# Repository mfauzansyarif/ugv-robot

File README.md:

# UGV Lidikzi 2

Sistem kendali *Unmanned Ground Vehicle* (UGV) remote-control untuk TNI Zeni AD. Robot dikendalikan operator lewat GCS (Ground Control Station) touchscreen yang terhubung ke robot lewat radio RF, dengan STM32 sebagai "hub" hardware dan Jetson Nano (ROS2) sebagai "otak" pengambil keputusan.

Dokumentasi ini mencakup arsitektur, protokol komunikasi, cara build/flash/jalanin tiap komponen, dan tools testing yang tersedia.

---

## Daftar Isi

1. [Ringkasan Fitur](#ringkasan-fitur)
2. [Arsitektur Sistem](#arsitektur-sistem)
3. [Struktur Repository](#struktur-repository)
4. [Komponen Hardware](#komponen-hardware)
5. [Protokol Komunikasi](#protokol-komunikasi)
6. [Firmware STM32](#firmware-stm32)
7. [ROS2 (Jetson Nano)](#ros2-jetson-nano)
8. [GCS App (Ground Control Station)](#gcs-app-ground-control-station)
9. [Cara Build & Flash STM32](#cara-build--flash-stm32)
10. [Cara Jalankan ROS2](#cara-jalankan-ros2)
11. [Cara Jalankan GCS App](#cara-jalankan-gcs-app)
12. [Tools Testing](#tools-testing)
13. [Isu & Catatan Penting](#isu--catatan-penting)

---

## Ringkasan Fitur

- Kendali gerak (drive + steering) lewat joystick analog di panel GCS
- 8 actuator linear individual (steering depan/belakang kiri-kanan, body depan/belakang kiri-kanan) - bisa dikalibrasi satu-satu, atau digerakkan berpasangan per-axle buat kenyamanan
- Pan-tilt kamera + zoom (Sony FCB-EV7520 lewat modul joystick/RS485)
- Laser Range Finder (Noptel LRF127) - baca jarak on-demand + pointer ON/OFF - ⚠️ **masih develop, lihat [Isu & Catatan Penting](#isu--catatan-penting)**
- Lampu depan (dimmable) + lampu belakang (mati/nyala/kedip, otomatis kedip pas mundur)
- Slip ring power switch (buat pantilt+kamera+LRF yang duduk di dudukan berputar) - ⚠️ **butuh jeda tunggu setelah dinyalain, lihat [Isu & Catatan Penting](#isu--catatan-penting)**
- Mode kalibrasi actuator (Fully Extend + Fully Left) - ⚠️ **durasi timeout-nya belum di-set, lihat [Isu & Catatan Penting](#isu--catatan-penting)**
- Deteksi orang otomatis (YOLO/TensorRT) buat overlay video, mode manual/auto - ⚠️ **masih develop, belum diimplementasi (butuh spek Jetson lebih tinggi)**
- E-STOP manual + beberapa lapis failsafe otomatis (link timeout, auto-estop kalau telemetry putus, dll - lihat [Isu & Catatan Penting](#isu--catatan-penting))

---

## Arsitektur Sistem

Prinsip desain: **"dumb driver, smart brain"** - STM32 gak pernah mutusin apa-apa sendiri (kecuali failsafe darurat), semua logic ada di `core_node.py` (Jetson). STM32 cuma nge-apply command final dan me-relay data mentah.

```mermaid
flowchart LR
    subgraph GCS["GCS Touchscreen (Asus NUC / laptop)"]
        Arduino["Arduino Mega Pro<br/>(panel fisik: joystick,<br/>tombol, switch)"]
        App["GCS App (PySide6)<br/>main.py / main_window.py"]
        Arduino -- "Serial USB<br/>(frame mentah panel)" --> App
    end

    App == "RF Radio<br/>USART2 @ 57600<br/>15B request / 11B reply<br/>+ checksum" ==> STM

    subgraph STM["STM32 G474RE (HUB)"]
        direction TB
        M["main.c<br/>dumb driver + failsafe"]
    end

    STM == "UART langsung<br/>USART3 @ 115200<br/>27B down / 20B up<br/>+ checksum XOR" ==> Jetson

    subgraph Jetson["Jetson Nano (OTAK - ROS2)"]
        direction TB
        SIN["stm32_interface_node<br/>(translator byte<->topic)"]
        CN["core_node<br/>(SATU-SATUNYA logic)"]
        SIN <-. topics .-> CN
    end

    STM == "RS485 bus<br/>USART1 @ 9600<br/>Pelco-D style, 7B/frame" ==> RS485

    subgraph RS485["Bus RS485 Bersama"]
        Pantilt["Pantilt<br/>(protokol custom)"]
        Kamera["Kamera<br/>Sony FCB-EV7520<br/>(Pelco-D->VISCA)"]
        Bridge["Bridge LRF<br/>NUCLEO-G431KB<br/>(addr=2)"]
    end

    Bridge -- "UART langsung<br/>native protocol" --> LRF["LRF127 (Noptel)<br/>laser rangefinder"]

    STM -- "Motor driver" --> Motors["4x Motor AC (PULS+SIGN)<br/>Houle Servo Driver"]
    STM -- "H-bridge digital" --> Act["8x Linear Actuator<br/>TiMOTION JP4"]
    STM -- PWM --> Lamps["Lampu depan/belakang"]
```

**Kenapa arsitektur ini:** desain awal sempat coba SPI dan I2C langsung ke Jetson, gagal secara elektrik. Mentor minta USB Jetson jangan dipakai buat link real-time (cuma boleh buat flashing sesekali) - jadi semua link fisik (RF, RS485) dipegang STM32, Jetson cuma dapat 1 link UART biasa ke STM32.

Node `cv_node` (deteksi orang YOLO/TensorRT) direncanakan tapi **belum diimplementasi** - lihat [Isu & Catatan Penting](#isu--catatan-penting).

Diagram block versi visual (drawio) juga ada di [`Dokumentasi/Block Diagram.png`](Dokumentasi/Block%20Diagram.png).

---

## Struktur Repository

Repo sudah dirapikan jadi struktur flat tunggal - semua yang ada di root INI yang aktif dipakai, gak ada lagi folder arsip/duplikat legacy.

```
ugv-robot/
├── Code/
│   ├── NucleoG474RE/           # Firmware STM32 G474RE (MASTER/HUB) - STM32CubeIDE project
│   ├── NucleoG431KB/           # Firmware STM32 G431KB (BRIDGE LRF) - STM32CubeIDE project
│   ├── ArduinoMegaPro/         # Firmware panel GCS fisik (joystick+tombol -> serial)
│   ├── Asus NUC/               # GCS App (PySide6, Python) - jalan di laptop/NUC
│   └── Jetson Nano/            # (kosong - node ROS2 ada di ROS2/ros2_ws, bukan di sini)
├── Datasheet/                  # Datasheet semua komponen (LRF127, servo driver, actuator, dst)
├── Dokumentasi/                # Block diagram + dokumentasi lama
├── Hardware/                   # Layout panel GCS, gambar rangka
├── ROS2/
│   ├── PANDUAN_JALANKAN_ROS2.txt
│   └── ros2_ws/                # Workspace ROS2 (src/ + build/install/log kalau sudah di-colcon build)
├── Schematic/                  # Skematik KiCad/EasyEDA board custom STM32G474
└── Test Code/                  # Kumpulan skrip tes Python/Arduino (satu lokasi, histori lengkap)
```

---

## Komponen Hardware

| Komponen | Model | Peran |
|---|---|---|
| MCU Hub | STM32G474RE (custom board berbasis Nucleo) | Master - kendaliin motor, actuator, lampu, relay semua link |
| MCU Bridge LRF | STM32G431KB (Nucleo) | Translator LRF127 <-> bus RS485 - ⚠️ board fisik lagi rusak |
| Compute utama | NVIDIA Jetson Nano 4GB (JetPack 4.x) | Jalanin ROS2 (logic + computer vision) |
| Panel GCS | Arduino Mega 2560 Pro | Baca joystick analog + tombol panel fisik |
| Laptop/GCS | Asus NUC / laptop Windows | Jalanin GCS App (PySide6) |
| Motor drive | 4x AC Servo Motor + Houle "HK Series" Servo Driver | Gerak maju/mundur (PULS+SIGN interface) |
| Actuator steering/body | 8x TiMOTION JP4 Linear Actuator | Steering (4x) + naik-turun body (4x) |
| Laser Rangefinder | Noptel LRF127 | Ukur jarak target |
| Kamera | Sony FCB-EV7520 (+ modul joystick/RS485-VISCA) | Video + zoom, kontrol Pelco-D |
| Pan-Tilt | Custom (protokol reverse-engineered) | Gerak kamera+LRF |
| Video link | RC832 Video Receiver | Terima video analog di sisi GCS |
| Radio | Modul RF custom (57600 baud) | Link GCS <-> STM32 |

Semua datasheet ada di [`Datasheet/`](Datasheet/).

---

## Protokol Komunikasi

Ada 4 link fisik terpisah, semua checksummed:

### 1. GCS ↔ STM32 (Radio RF, USART2 @ 57600 baud)

Request-response, GCS yang mulai duluan (~20Hz).

**GCS → STM32, 15 byte** (`"=BbbbbbBBBBbBbBB"`):

| Field | Tipe | Keterangan |
|---|---|---|
| `estop` | uint8 | 0/1 |
| `xJoy1`, `yJoy1` | int8 | Joystick analog utama (steer/speed), -100..100 |
| `xJoy2`, `yJoy2` | int8 | Tombol digital pantilt, -100/0/100 |
| `zoom` | int8 | -1/0/1 |
| `lrf` | uint8 | Trigger hold-to-laser / release-to-read |
| `fLamp`, `bLamp` | uint8 | Brightness/mode lampu |
| `slipRing` | uint8 | 0/1 |
| `bodyUpDown` | int8 | Raise/Lower body (tombol fisik) |
| `motorIndividualId` | uint8 | 0=normal, 1-10=override individual/berpasangan (lihat `motor_linear_dialog.py`) |
| `motorIndividualArah` | int8 | -1/0/1 |
| `kalibrasi` | uint8 | 0/1 |
| `mode` | uint8 | 0=manual, 1=auto (gerbang CV - belum fungsional, `cv_node` belum diimplementasi) |

**STM32 → GCS, 11 byte**: `[0xA5][stm32_status][lrf_status][lrf_lsb][lrf_msb][box_terdeteksi][box_x][box_y][box_w][box_h][checksum XOR]`

### 2. Jetson ↔ STM32 (UART langsung, USART3 @ 115200 baud)

Jetson yang inisiatif tiap siklus (~10-20Hz), synchronous write-then-read. Reception di STM32 pakai **hitung-byte-manual** (bukan idle-line), karena link ini sensitif ke jeda antar-byte dari buffering OS/USB Jetson.

**Jetson → STM32 (down), 27 byte**: `speed(1) + act[8](8) + fLamp,bLamp,bLampMode(3) + pantiltH,pantiltV,zoom(3) + slipRing,lrfTrigger(2) + gcsReply x4(4) + gcsReplyBox x5(5) + checksum(1)`

**STM32 → Jetson (up), 20 byte**: 15 byte relay GCS mentah + `lrfLsb,lrfMsb,lrfStatus,stm32Status(4)` + `checksum(1)`

Checksum kedua arah: XOR semua byte data (belum termasuk byte checksum-nya sendiri).

### 3. STM32 ↔ Bus RS485 (USART1 @ 9600 baud)

Frame custom mirip Pelco-D, 7 byte: `[0xFF][alamat][cmd1][cmd2][data1][data2][checksum]` (checksum = additive sum, khusus pantilt payload 0xFF diabaikan dari sum). Alamat: kamera=1, bridge LRF=2, pantilt gak validasi alamat (payload beda struktur).

Baca jarak LRF & set pointer **non-blocking (async)** di firmware - request dikirim, main loop STM32 TETAP jalan normal, balasan dicek lewat interrupt + timeout (dulu blocking, bikin STM32 "beku" 1.3-2.3 detik tiap kali LRF diminta - lihat [Isu & Catatan Penting](#isu--catatan-penting)).

### 4. Bridge (G431KB) ↔ LRF127

Protokol native LRF127 (lihat [`Datasheet/LRF127 Interface Control.pdf`](Datasheet/LRF127%20Interface%20Control.pdf)), mode SMM (~1.3 detik nominal, +300ms kemungkinan cuaca buruk). Bridge translate hasilnya jadi frame Pelco-D-style 7-byte buat dikirim balik ke bus.

### Sequence: baca jarak LRF (async)

```mermaid
sequenceDiagram
    participant Op as Operator (GCS)
    participant Jetson as Jetson (core_node)
    participant STM as STM32 G474RE
    participant Bridge as Bridge G431KB
    participant LRF as LRF127

    Op->>Jetson: lepas tombol LRF (release edge)
    Jetson->>STM: down-frame, lrfTrigger=BACA_JARAK
    STM->>Bridge: request jarak (RS485, non-blocking)
    Note over STM: main loop TETAP jalan -<br/>balas GCS & Jetson normal
    Bridge->>LRF: query native protocol
    LRF-->>Bridge: jarak + status (~1.3-1.6 detik)
    Bridge-->>STM: respons 7 byte (interrupt RX)
    Note over STM: CekBalasanLrf() proses<br/>di loop berikutnya
    STM-->>Jetson: up-frame, lrfJarak + lrfStatus
    Jetson-->>Op: tampil jarak di GCS App
```

---

## Firmware STM32

### G474RE (`Code/NucleoG474RE/Core/Src/main.c`) - Master/Hub

- Pegang LANGSUNG: radio GCS (USART2), bus RS485 (USART1), semua motor/actuator/lampu, link Jetson (USART3), debug (LPUART1 @ 209700, numpang ST-LINK VCP di PA2/PA3).
- **2 failsafe independen**: `JETSON_LINK_TIMEOUT_MS` (500ms) dan `GCS_LINK_TIMEOUT_MS` (1500ms, sengaja lebih longgar - radio RF normalnya miss ~75-80% per percobaan) - kalau salah satu link mati total, paksa stop motor/actuator.
- Anti-glitch: `setPulseFreq()` cuma di-re-apply kalau nilai speed BERUBAH (hindari reprogram timer redundan ~20Hz), debounce 1-frame khusus transisi speed->0.
- Motor AC: `setMotor()` -> Timer Output-Compare Toggle mode (`TIM3/TIM4/TIM8/TIM15`), `freqHz = |speed| * FREQ_PER_RPM(50)`, clock 170MHz.
- Actuator: `SetActuator()` - 2 pin digital (RPWM/LPWM) per actuator, gak ada feedback posisi (jog control murni).

### G431KB (`Code/NucleoG431KB/Core/Src/main.c`) - Bridge LRF

- Address 2 di bus RS485 bersama.
- Translate command Pelco-D-style dari bus -> protokol native LRF127 (USART2-nya sendiri, terpisah dari bus) -> bungkus hasil balik jadi Pelco-D-style.
- `LRF_FlushRx()` sebelum tiap command - cegah bug "sekali gagal, gagal selamanya" dari byte basi nyangkut di buffer.

### Arduino Mega Pro (`Code/ArduinoMegaPro/ArduinoMegaPro.ino`) - Panel GCS

Baca joystick analog (averaging + exponential smoothing + deadzone) dan tombol panel, kirim frame mentah 20Hz ke GCS App lewat USB serial.

---

## ROS2 (Jetson Nano)

2 node aktif sekarang, pembagian tugas TEGAS - **cuma `core_node` yang boleh punya logic/keputusan**.

```mermaid
flowchart LR
    STM32I["stm32_interface_node<br/>(translator murni)"] -- "/stm32/gcs_relay<br/>/stm32/lrf_status<br/>/stm32/health" --> Core
    Core["core_node<br/>(SATU-SATUNYA logic)"] -- "/stm32/command" --> STM32I
```

| Node | Boleh logic? | Tugas |
|---|---|---|
| `stm32_interface_node.py` | Tidak | Baca/tulis serial ke STM32, publish data mentah, subscribe command final |
| `core_node.py` | **Ya** | Olah semua data mentah jadi command final |

> ⚠️ **`cv_node` (deteksi orang YOLO/TensorRT) belum diimplementasi** - direncanakan sebagai node ke-3, publish ke `core_node` lewat topic `/vision/deteksi`, tapi masih tahap develop dan butuh spek Jetson lebih tinggi dari yang sekarang (Nano 4GB) biar YOLO+video gak nge-lag decision loop utama. Field `mode` (manual/auto) di protokol GCS↔STM32 sudah disiapkan buat fitur ini, belum ada consumer-nya.

Detail lengkap mapping field-per-field ada di komentar/docstring tiap node (`ROS2/ros2_ws/src/`) dan di [`ROS2/PANDUAN_JALANKAN_ROS2.txt`](ROS2/PANDUAN_JALANKAN_ROS2.txt) - baca ini dulu sebelum ubah node manapun.

**Jetson Nano 4GB, bukan Orin Nano** - JetPack 4.x = Ubuntu 18.04, jadi ROS2 yang dipakai **Foxy** (bukan Humble, butuh 22.04).

---

## GCS App (Ground Control Station)

`Code/Asus NUC/`, PySide6. Entry point `main.py`.

- `main_window.py` - window utama: panel Connection (GCS Board/Telemetry/Controller), Control Panel (lampu, slip ring, body), Camera Viewer, dialog Motor Linear Individual.
- `motor_linear_dialog.py` - kontrol per-actuator (Steer/Body, masing-masing Extend/Retract) + mode berpasangan (Steer Together).
- `serial_workers.py` - 2 thread terpisah: `ArduinoReader` (baca panel fisik) dan `RFLink` (kirim/terima ke STM32, 20Hz).
- `camera_viewer.py` - render video RTSP/analog + overlay box deteksi.
- Auto E-STOP kalau app ditutup ATAU telemetry gak respons (link masih kirim command tapi gak ada balasan) - lihat [Isu & Catatan Penting](#isu--catatan-penting).

---

## Cara Build & Flash STM32

Butuh **STM32CubeIDE**.

1. Buka STM32CubeIDE, `File > Open Projects from File System`, arahkan ke `Code/NucleoG474RE` (atau `NucleoG431KB` buat bridge LRF).
2. `Project > Build Project` (atau klik ikon palu). Pastikan **0 error**.
3. Colok board via USB (ST-LINK bawaan Nucleo), klik **Run/Debug** (ikon play/bug) buat flash.
4. Debug log bisa dipantau lewat micro-USB yang SAMA (numpang ST-LINK Virtual COM Port) - buka terminal serial (PuTTY dkk) di port yang muncul, **baudrate 209700**, 8N1.

> **Urutan flash pas ganti protokol**: kalau ngubah format frame (misal nambah checksum), STM32 G474RE, `stm32_interface_node.py` (Jetson), dan GCS App harus di-update BARENG - kalau salah satu ketinggalan versi lama, semua link bakal keliatan "putus" padahal cuma beda protokol.

---

## Cara Jalankan ROS2

Jalan di Jetson Nano lewat Docker (ROS2 Foxy di dalam container). Operasional harian **otomatis** - `ugv_robot.service` (systemd) nyalain container + kedua node begitu Jetson boot, gak perlu ngetik apa-apa.

Cek cepat robot udah jalan otomatis apa belum:

```bash
sudo docker ps                                # harus ada 1 baris "ugv_robot_container"
sudo journalctl -u ugv_robot.service -n 30    # cari "Core Node siap" & "Serial terbuka di ..."
```

Parameter yang bisa dituning tanpa edit kode (lihat komentar di `core_node.py` buat daftar lengkap), contoh:

```bash
ros2 run ugv_robot core_node --ros-args -p steer_threshold:=20
```

Diagnostik cepat (dari dalam container - lihat panduan buat cara masuknya):

```bash
ros2 node list                 # pastikan kedua node kedaftar
ros2 topic hz /stm32/command   # pastikan core_node beneran publish rutin
ros2 topic echo /stm32/health  # cek status link STM32 real-time
```

Panduan LENGKAP ada di [`ROS2/PANDUAN_JALANKAN_ROS2.txt`](ROS2/PANDUAN_JALANKAN_ROS2.txt) - mulai dari nyalain Jetson dari nol (buat yang belum pernah pegang sama sekali) sampai mode manual/development (`docker run` dari nol, `colcon build`, jalanin node satu-satu, tes manual tanpa `core_node`).

---

## Cara Jalankan GCS App

Di laptop/NUC Windows:

```powershell
cd "Code\Asus NUC"
pip install PySide6 pyserial opencv-python
python main.py
```

App langsung fullscreen (`Esc` buat keluar fullscreen, `F11` balik lagi). Setting port (COM Arduino, COM/radio RF, dsb) ada di `config.py`/`config.json`, atau lewat tombol Settings di app.

---

## Tools Testing

Semua skrip test Python/Arduino ada di [`Test Code/`](Test%20Code/) (satu lokasi, histori lengkap termasuk versi lama):

| Skrip | Fungsi |
|---|---|
| `test_gcs_manual_g474.py` | Laptop pura-pura jadi GCS, set field manual (`set xjoy1 50` dst) - buat tes STM32 tanpa GCS App/radio |
| `test_gcs_lengkap_manual_g474.py` | Sama, tapi mereplikasi logic terjemahan `_bangun_frame_gcs()` app asli (dari state mentah joystick) |
| `test_jetson_manual_g474.py` | Laptop pura-pura jadi Jetson lewat USB-TTL langsung - isolasi masalah tanpa Jetson asli |
| `test_bus_pantilt_kamera_lrf.py` | Kontrol manual pantilt/kamera/LRF-bridge langsung ke bus RS485 (tanpa STM32) |
| `test_loopback_usb_ttl.py` | Validasi 1 modul USB-TTL (self-loopback, RX dijumper ke TX-nya sendiri) |
| `test_loopback_rs485_2_port.py` | Validasi 2 modul RS485 fisik terpisah (loopback lewat kabel RS485 asli) |
| `test_loopback_rs485_ke_ttl.py` | Validasi modul konverter RS485-to-TTL (diapit adapter USB-RS485 & USB-TTL) |
| `test_relay_serial_dua_arah.py` | Relay transparan dua arah (dulu buat gantiin kabel RF yang hilang) |

Setiap skrip punya docstring lengkap di bagian atas file (wiring, command yang tersedia, kapan dipakai).

---

## Isu & Catatan Penting

### Belum kelar / masih development

- **MCU Bridge LRF (G431KB) lagi RUSAK** - board fisiknya bermasalah (bukan soal firmware), LRF non-fungsional total sampai board ini diperbaiki/diganti.
- **LRF masih tahap develop** - interface komunikasi ke LRF127 yang sekarang (lewat bridge G431KB, Pelco-D-style di bus RS485) perlu dirombak jadi interface baru, belum final.
- **Slip ring ON butuh jeda tunggu, bisa sampai ~1 menit** - dugaan kuat dari kamera yang baru boot (transceiver RS485-nya belum settle). Mitigasi software `SLIPRING_GRACE_MS` (2 detik default, STM32 sengaja diam dari RS485 sesaat setelah slip ring nyala) **JAUH DARI CUKUP** - dari observasi lapangan operator tetap harus nunggu manual sampai ~1 menit sebelum pakai pantilt/kamera/LRF. Root cause di hardware kamera/slip ring belum diperbaiki.
- **Deteksi orang otomatis (YOLO/TensorRT) belum diimplementasi** - direncanakan lewat `cv_node`, masih tahap develop, blocked butuh spek Jetson lebih tinggi dari yang sekarang (Nano 4GB) biar YOLO+video gak nge-lag decision loop utama.
- **Timeout kalibrasi & proteksi stall actuator belum di-set** - mode kalibrasi (Fully Extend + Fully Left) dan proteksi stall umum buat actuator sama-sama butuh durasi timeout yang belum ditentuin. Actuator linear gak punya feedback posisi, jadi kalau macet di ujung stroke bisa overheat/kebakar (pernah nyaris kejadian). Blocked butuh estimasi durasi full-stroke actuator yang terkonfirmasi ke hardware asli (datasheet JP4 kasih estimasi ~6-7 detik, belum divalidasi).
- **Failsafe GCS vs miss rate RF asli** - `GCS_LINK_TIMEOUT_MS=1500ms` belum terverifikasi langsung ke radio asli (miss rate normalnya 75-80%/percobaan menurut catatan `serial_workers.py`). Perlu tes ulang begitu radio bisa diakses.

### Sudah diperbaiki (histori, buat konteks)

- **Baca LRF dulu BLOCKING** - sempat bikin STM32 "beku" total 1.3-2.3 detik tiap kali diminta jarak (semua link keliatan disconnect). Diperbaiki jadi async/non-blocking (lihat `CekBalasanLrf()` di `main.c`).
- **Auto E-STOP kalau GCS App gak dapat balasan** - `_on_jetson_terputus()` di `main_window.py` paksa ESTOP begitu 10x berturut gak dapat balasan (~1 detik), sticky sampai operator lepas manual. Ini nutup celah "STM32 masih nerima command valid, mobil jalan terus, tapi GCS gak bisa lihat konfirmasinya".
- **Kalibrasi steering per-actuator individual** - motor_id 1-4 (steering) dan 5-8 (body) sekarang semuanya individual (gak berpasangan lagi), plus id 9-10 buat gerak sepasang axle sekaligus (kenyamanan, bukan presisi kalibrasi).
- **Checksum Jetson↔STM32** ditambahkan (XOR) buat nutup celah data corruption yang sebelumnya gak kedeteksi sama sekali di link itu.

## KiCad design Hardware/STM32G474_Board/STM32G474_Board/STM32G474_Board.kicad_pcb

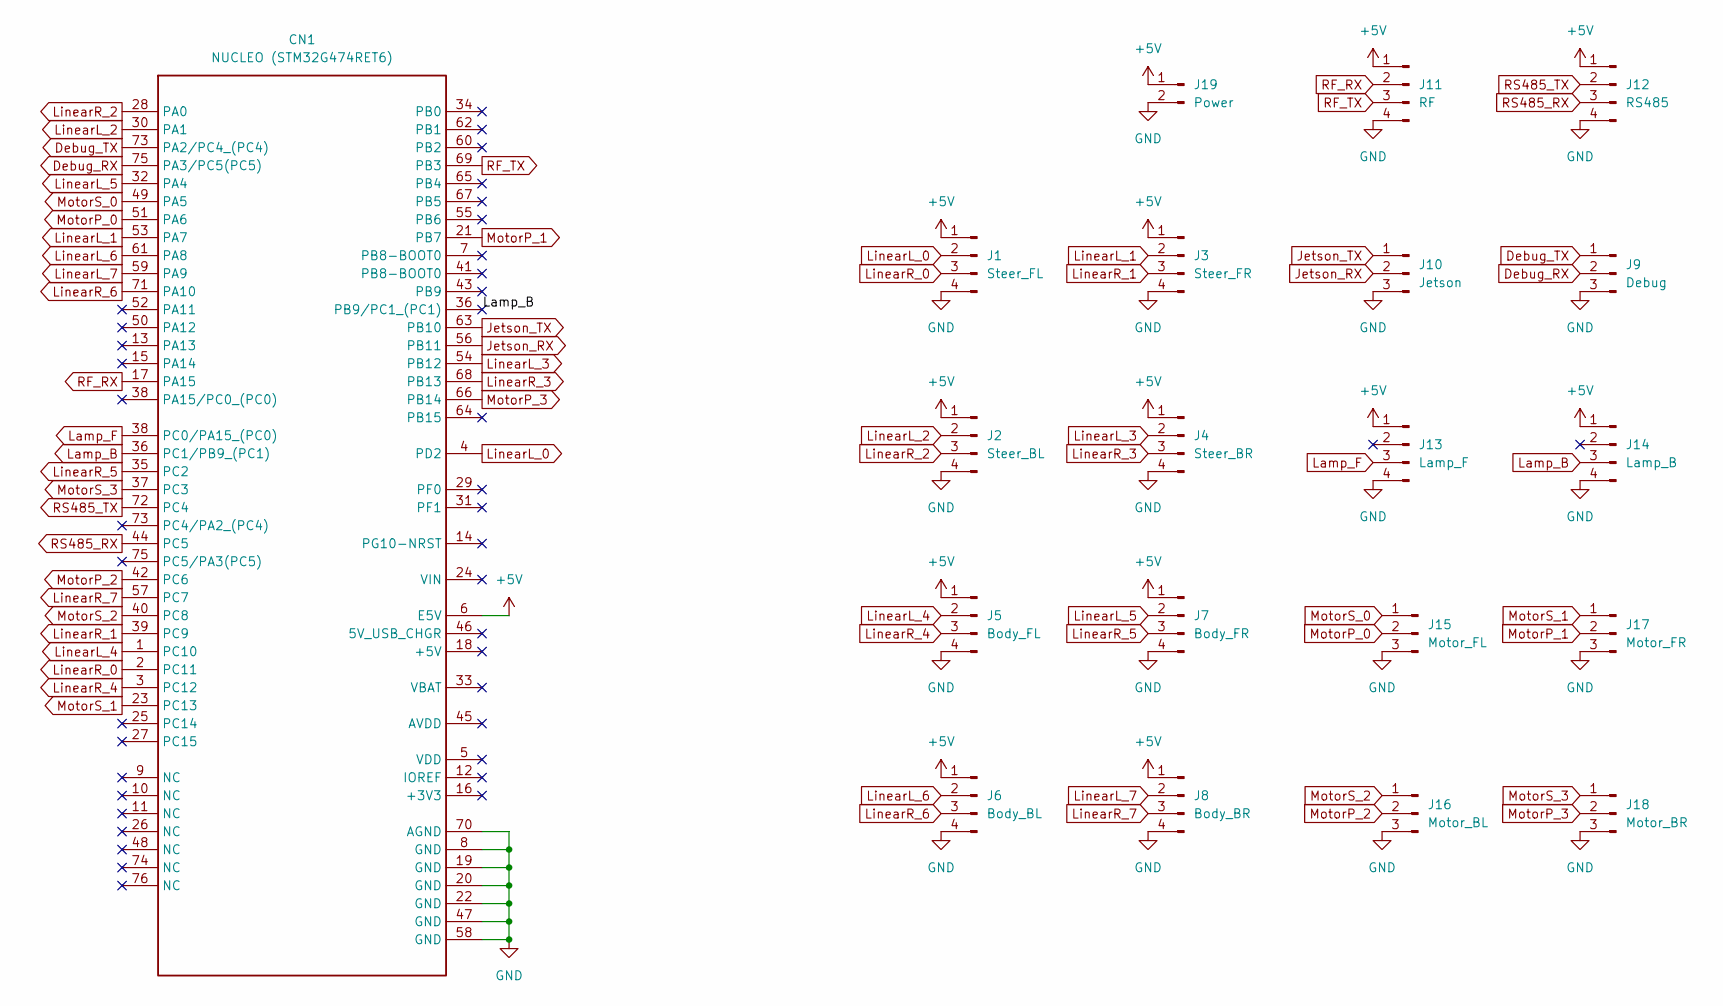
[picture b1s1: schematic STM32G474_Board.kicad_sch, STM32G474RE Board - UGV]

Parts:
CN1: NUCLEO (STM32G474RET6); NUCLEO-G474RE; Manufacturer Part NUCLEO-G474RE
J1: Steer_FL; JST_XH_B4B-XH-A_1x04_P2.50mm_Vertical
J2: Steer_BL; JST_XH_B4B-XH-A_1x04_P2.50mm_Vertical
J3: Steer_FR; JST_XH_B4B-XH-A_1x04_P2.50mm_Vertical
J4: Steer_BR; JST_XH_B4B-XH-A_1x04_P2.50mm_Vertical
J5: Body_FL; JST_XH_B4B-XH-A_1x04_P2.50mm_Vertical
J6: Body_BL; JST_XH_B4B-XH-A_1x04_P2.50mm_Vertical
J7: Body_FR; JST_XH_B4B-XH-A_1x04_P2.50mm_Vertical
J8: Body_BR; JST_XH_B4B-XH-A_1x04_P2.50mm_Vertical
J9: Debug; JST_XH_B3B-XH-A_1x03_P2.50mm_Vertical
J10: Jetson; JST_XH_B3B-XH-A_1x03_P2.50mm_Vertical
J11: RF; JST_XH_B4B-XH-A_1x04_P2.50mm_Vertical
J12: RS485; JST_XH_B4B-XH-A_1x04_P2.50mm_Vertical
J13: Lamp_F; JST_XH_B4B-XH-A_1x04_P2.50mm_Vertical
J14: Lamp_B; JST_XH_B4B-XH-A_1x04_P2.50mm_Vertical
J15: Motor_FL; JST_XH_B3B-XH-A_1x03_P2.50mm_Vertical
J16: Motor_BL; JST_XH_B3B-XH-A_1x03_P2.50mm_Vertical
J17: Motor_FR; JST_XH_B3B-XH-A_1x03_P2.50mm_Vertical
J18: Motor_BR; JST_XH_B3B-XH-A_1x03_P2.50mm_Vertical
J19: Power; JST_XH_B2B-XH-A_1x02_P2.50mm_Vertical

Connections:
+5V: CN1.6 (E5V), J1.1, J2.1, J3.1, J4.1, J5.1, J6.1, J7.1, J8.1, J11.1, J12.1, J13.1, J14.1, J19.1
Debug_RX: CN1.75 (PA3/PC5(PC5)), J9.2
Debug_TX: CN1.73 (PA2/PC4_(PC4)), J9.1
GND: CN1.8 (GND), CN1.19 (GND), CN1.20 (GND), CN1.22 (GND), CN1.47 (GND), CN1.58 (GND), CN1.70 (AGND), J1.4, J2.4, J3.4, J4.4, J5.4, J6.4, J7.4, J8.4, J9.3, J10.3, J11.4, J12.4, J13.4, J14.4, J15.3, J16.3, J17.3, J18.3, J19.2
Jetson_RX: CN1.56 (PB11), J10.2
Jetson_TX: CN1.63 (PB10), J10.1
Lamp_B: CN1.36 (PC1/PB9_(PC1)), J14.3
Lamp_F: CN1.38 (PC0/PA15_(PC0)), J13.3
LinearL_0: CN1.4 (PD2), J1.2
LinearL_1: CN1.53 (PA7), J3.2
LinearL_2: CN1.30 (PA1), J2.2
LinearL_3: CN1.54 (PB12), J4.2
LinearL_4: CN1.1 (PC10), J5.2
LinearL_5: CN1.32 (PA4), J7.2
LinearL_6: CN1.61 (PA8), J6.2
LinearL_7: CN1.59 (PA9), J8.2
LinearR_0: CN1.2 (PC11), J1.3
LinearR_1: CN1.39 (PC9), J3.3
LinearR_2: CN1.28 (PA0), J2.3
LinearR_3: CN1.68 (PB13), J4.3
LinearR_4: CN1.3 (PC12), J5.3
LinearR_5: CN1.35 (PC2), J7.3
LinearR_6: CN1.71 (PA10), J6.3
LinearR_7: CN1.57 (PC7), J8.3
MotorP_0: CN1.51 (PA6), J15.2
MotorP_1: CN1.21 (PB7), J17.2
MotorP_2: CN1.42 (PC6), J16.2
MotorP_3: CN1.66 (PB14), J18.2
MotorS_0: CN1.49 (PA5), J15.1
MotorS_1: CN1.23 (PC13), J17.1
MotorS_2: CN1.40 (PC8), J16.1
MotorS_3: CN1.37 (PC3), J18.1
RF_RX: CN1.17 (PA15), J11.2
RF_TX: CN1.69 (PB3), J11.3
RS485_RX: CN1.44 (PC5), J12.3
RS485_TX: CN1.72 (PC4), J12.2

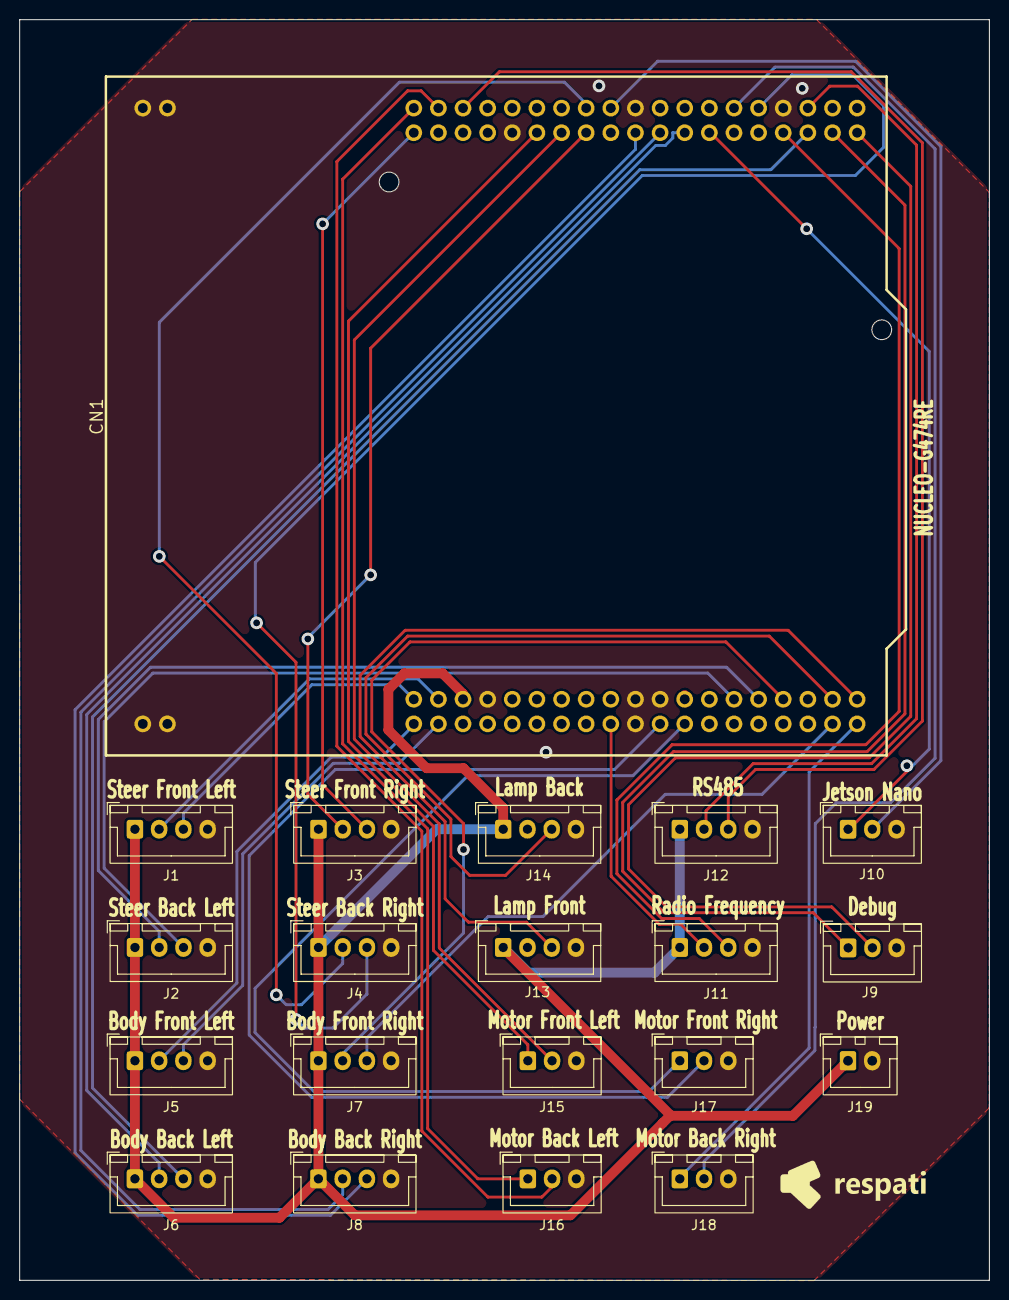
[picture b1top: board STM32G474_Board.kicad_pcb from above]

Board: 2 copper layers, 100.0 x 130.0 mm, 20 parts (0 on the bottom side), 36 nets.

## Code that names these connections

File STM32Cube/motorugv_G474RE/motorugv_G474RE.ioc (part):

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Mcu.Name=STM32G474R(B-C-E)Tx
Mcu.Package=LQFP64
Mcu.UserName=STM32G474RETx
PA0.GPIOParameters=GPIO_Label
PA0.GPIO_Label=LinearR_2
PA0.Signal=GPIO_Output
PA1.GPIOParameters=GPIO_Label
PA1.GPIO_Label=LinearL_2
PA1.Signal=GPIO_Output
PA10.GPIOParameters=GPIO_Label
PA10.GPIO_Label=LinearR_6
PA10.Signal=GPIO_Output
PA11.Mode=Device
PA11.Signal=USB_DM
PA12.Mode=Device
PA12.Signal=USB_DP
PA13.GPIOParameters=GPIO_Label
PA13.GPIO_Label=T_SWDIO
PA13.Mode=Serial_Wire
PA13.Signal=SYS_JTMS-SWDIO
PA14.GPIOParameters=GPIO_Label
PA14.GPIO_Label=T_SWCLK
PA14.Mode=Serial_Wire
PA14.Signal=SYS_JTCK-SWCLK
PA15.GPIOParameters=GPIO_Label
PA15.GPIO_Label=RF_RX
PA15.Mode=Asynchronous
PA15.Signal=USART2_RX
PA2.GPIOParameters=GPIO_Label
PA2.GPIO_Label=Debug_TX
PA2.Mode=Asynchronous
PA2.Signal=LPUART1_TX
PA3.GPIOParameters=GPIO_Label
PA3.GPIO_Label=Debug_RX
PA3.Mode=Asynchronous
PA3.Signal=LPUART1_RX
PA4.GPIOParameters=GPIO_Label
PA4.GPIO_Label=LinearL_5
PA4.Signal=GPIO_Output
PA5.GPIOParameters=GPIO_Label
PA5.GPIO_Label=MotorS_0
PA5.Signal=GPIO_Output
PA6.GPIOParameters=GPIO_Label
PA6.GPIO_Label=MotorP_0
PA6.Signal=S_TIM3_CH1
PA7.GPIOParameters=GPIO_Label
PA7.GPIO_Label=LinearL_1
PA7.Signal=GPIO_Output
PA8.GPIOParameters=GPIO_Label
PA8.GPIO_Label=LinearL_6
PA8.Signal=GPIO_Output
PA9.GPIOParameters=GPIO_Label
PA9.GPIO_Label=LinearL_7
PA9.Signal=GPIO_Output
PB0.GPIOParameters=GPIO_Label
PB0.GPIO_Label=LED_Jetson
PB0.Signal=GPIO_Output
PB1.GPIOParameters=GPIO_Label
PB1.GPIO_Label=LED_RF
PB1.Signal=GPIO_Output
PB10.GPIOParameters=GPIO_Label
PB10.GPIO_Label=Jetson_TX
PB10.Mode=Asynchronous
PB10.Signal=USART3_TX
PB11.GPIOParameters=GPIO_PuPd,GPIO_Label
PB11.GPIO_Label=Jetson_RX
PB11.GPIO_PuPd=GPIO_PULLUP
PB11.Mode=Asynchronous
PB11.Signal=USART3_RX
PB12.GPIOParameters=GPIO_Label
PB12.GPIO_Label=LinearL_3
PB12.Signal=GPIO_Output
PB13.GPIOParameters=GPIO_Label
PB13.GPIO_Label=LinearR_3
PB13.Signal=GPIO_Output
PB14.GPIOParameters=GPIO_Label
PB14.GPIO_Label=MotorP_3
PB14.Signal=S_TIM15_CH1
PB2.GPIOParameters=GPIO_Label
PB2.GPIO_Label=LED_Heartbeat
PB2.Signal=GPIO_Output
PB3.GPIOParameters=GPIO_PuPd,GPIO_Label
PB3.GPIO_Label=RF_TX
PB3.GPIO_PuPd=GPIO_PULLUP
PB3.Mode=Asynchronous
PB3.Signal=USART2_TX
PB7.GPIOParameters=GPIO_Label
PB7.GPIO_Label=MotorP_1
PB7.Signal=S_TIM4_CH2
PC0.GPIOParameters=GPIO_Label
PC0.GPIO_Label=Lamp_F
PC0.Signal=S_TIM1_CH1
PC1.GPIOParameters=GPIO_Label
PC1.GPIO_Label=Lamp_B
PC1.Signal=S_TIM1_CH2
PC10.GPIOParameters=GPIO_Label
PC10.GPIO_Label=LinearL_4
PC10.Signal=GPIO_Output
PC11.GPIOParameters=GPIO_Label
PC11.GPIO_Label=LinearR_0
PC11.Signal=GPIO_Output
PC12.GPIOParameters=GPIO_Label
PC12.GPIO_Label=LinearR_4
PC12.Signal=GPIO_Output
PC13.GPIOParameters=GPIO_Label
PC13.GPIO_Label=MotorS_1
PC13.Signal=GPIO_Output
PC2.GPIOParameters=GPIO_Label
PC2.GPIO_Label=LinearR_5
PC2.Signal=GPIO_Output
PC3.GPIOParameters=GPIO_Label
PC3.GPIO_Label=MotorS_3
PC3.Signal=GPIO_Output
PC4.GPIOParameters=GPIO_Label
PC4.GPIO_Label=RS485_TX
PC4.Mode=Asynchronous
PC4.Signal=USART1_TX
PC5.GPIOParameters=GPIO_PuPd,GPIO_Label
PC5.GPIO_Label=RS485_RX
PC5.GPIO_PuPd=GPIO_PULLUP
PC5.Mode=Asynchronous
PC5.Signal=USART1_RX
PC6.GPIOParameters=GPIO_Label
PC6.GPIO_Label=MotorP_2
PC6.Signal=S_TIM8_CH1
PC7.GPIOParameters=GPIO_Label
PC7.GPIO_Label=LinearR_7
PC7.Signal=GPIO_Output
PC8.GPIOParameters=GPIO_Label
PC8.GPIO_Label=MotorS_2
PC8.Signal=GPIO_Output
PC9.GPIOParameters=GPIO_Label
PC9.GPIO_Label=LinearR_1
PC9.Signal=GPIO_Output
PD2.GPIOParameters=GPIO_Label
PD2.GPIO_Label=LinearL_0
PD2.Signal=GPIO_Output
RCC.HSE_VALUE=24000000
RCC.SYSCLKFreq_VALUE=170000000
RCC.SYSCLKSource=RCC_SYSCLKSOURCE_PLLCLK
board=NUCLEO-G474RE
boardIOC=true
